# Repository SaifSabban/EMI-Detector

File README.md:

# EMI-Detector
A simple Arduino EMI Detector PCB.
the project mainly following Collin Cunningham's [Video](https://www.youtube.com/watch?v=y1Bke3750WE).

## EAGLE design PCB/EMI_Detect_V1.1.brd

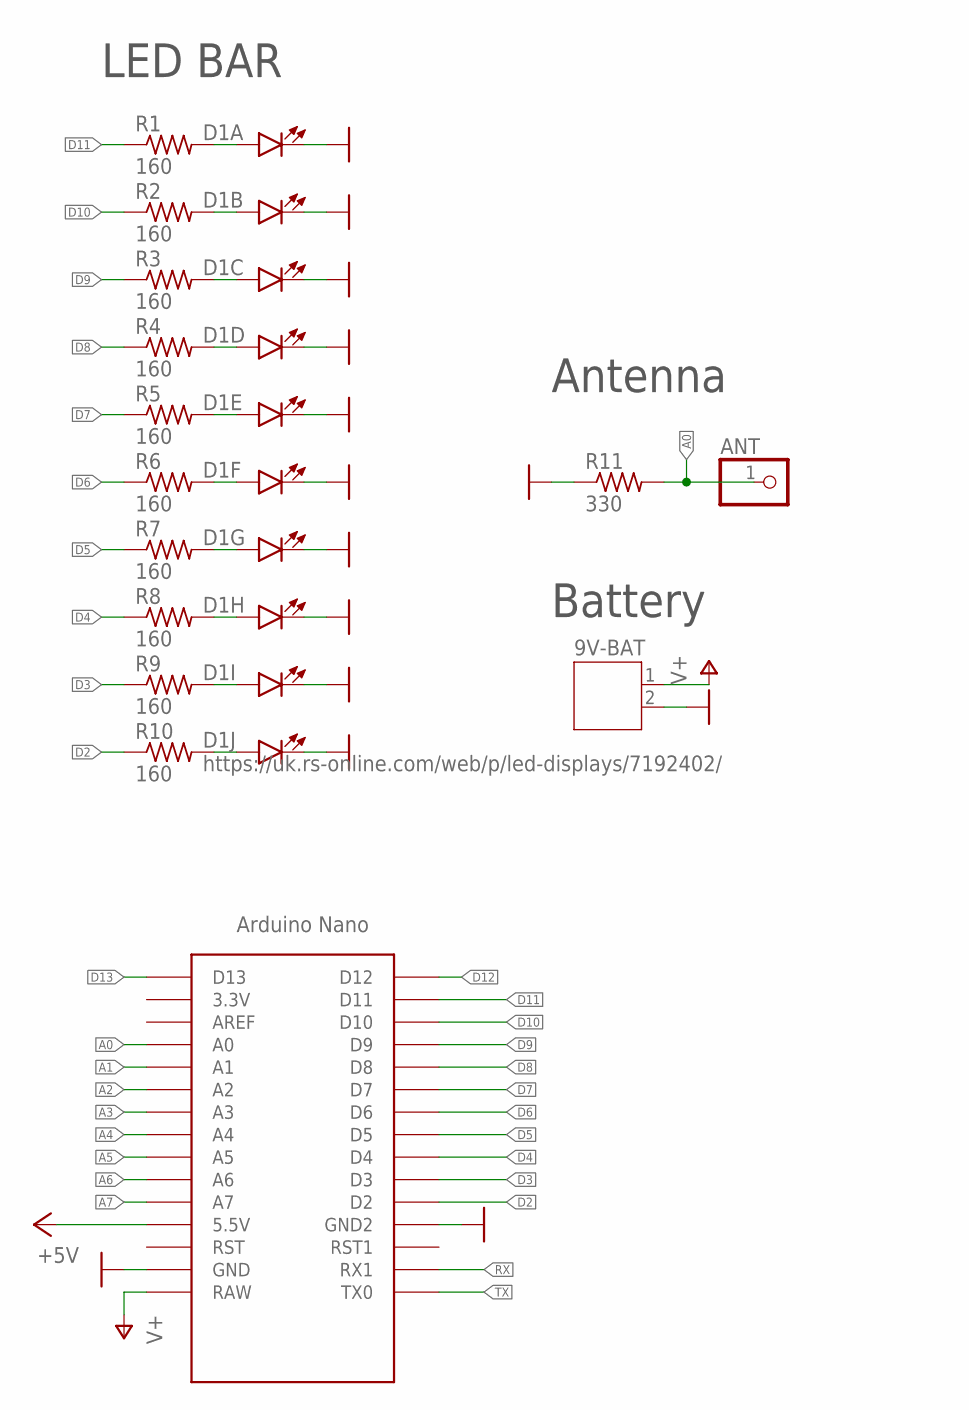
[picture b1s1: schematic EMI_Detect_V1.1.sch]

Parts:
9V-BAT: JST-PH2; JST-PH2-S2B
ANT: PINHD-1X1; 1X01
D1: https://uk.rs-online.com/web/p/led-displays/71924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; LED_BARGAPH_10
R1, R2, R3, R4, R5, R6, R7, R8, R9, R10: 160; R0603
R11: 330; R0603
U1: NANO

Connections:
+5V: U1.5V (5.5V)
A0: ANT.1, R11.2, U1.A0
A1: U1.A1
A2: U1.A2
A3: U1.A3
A4: U1.A4
A5: U1.A5
A6: U1.A6
A7: U1.A7
D2: R10.1, U1.D2
D3: R9.1, U1.D3
D4: R8.1, U1.D4
D5: R7.1, U1.D5
D6: R6.1, U1.D6
D7: R5.1, U1.D7
D8: R4.1, U1.D8
D9: R3.1, U1.D9
D10: R2.1, U1.D10
D11: R1.1, U1.D11
D12: U1.D12
D13: U1.D13
GND: 9V-BAT.2, D1.11 (C), D1.12 (C), D1.13 (C), D1.14 (C), D1.15 (C), D1.16 (C), D1.17 (C), D1.18 (C), D1.19 (C), D1.20 (C), R11.1, U1.GND, U1.GND1 (GND2)
unnamed: D1.1 (A), R1.2
unnamed: D1.2 (A), R2.2
unnamed: D1.3 (A), R3.2
unnamed: D1.4 (A), R4.2
unnamed: D1.5 (A), R5.2
unnamed: D1.6 (A), R6.2
unnamed: D1.7 (A), R7.2
unnamed: D1.8 (A), R8.2
unnamed: D1.9 (A), R9.2
unnamed: D1.10 (A), R10.2
RX: U1.RX1
TX: U1.TX0
V+: 9V-BAT.1, U1.RAW

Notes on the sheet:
LED BAR
Antenna
Battery

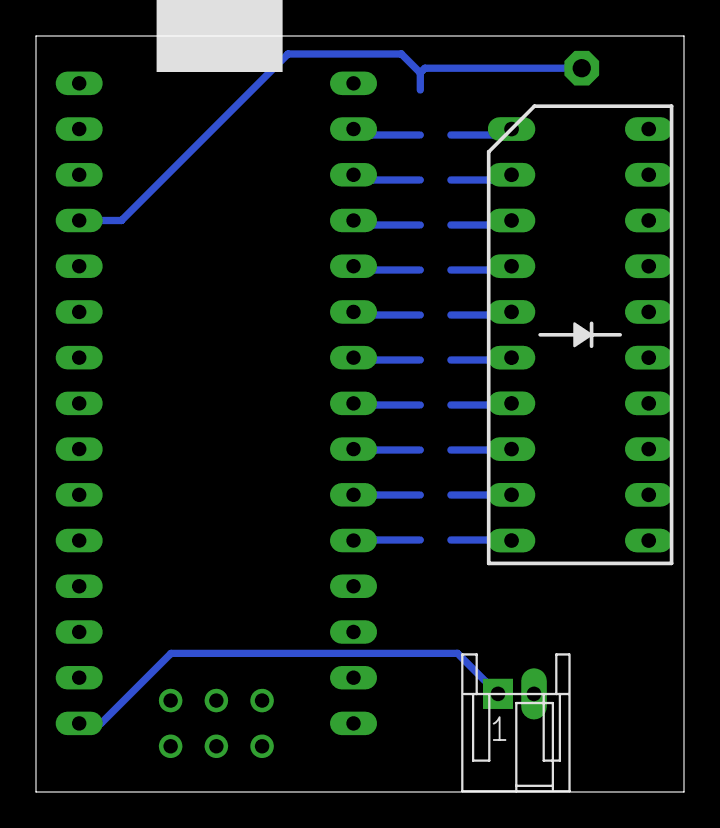
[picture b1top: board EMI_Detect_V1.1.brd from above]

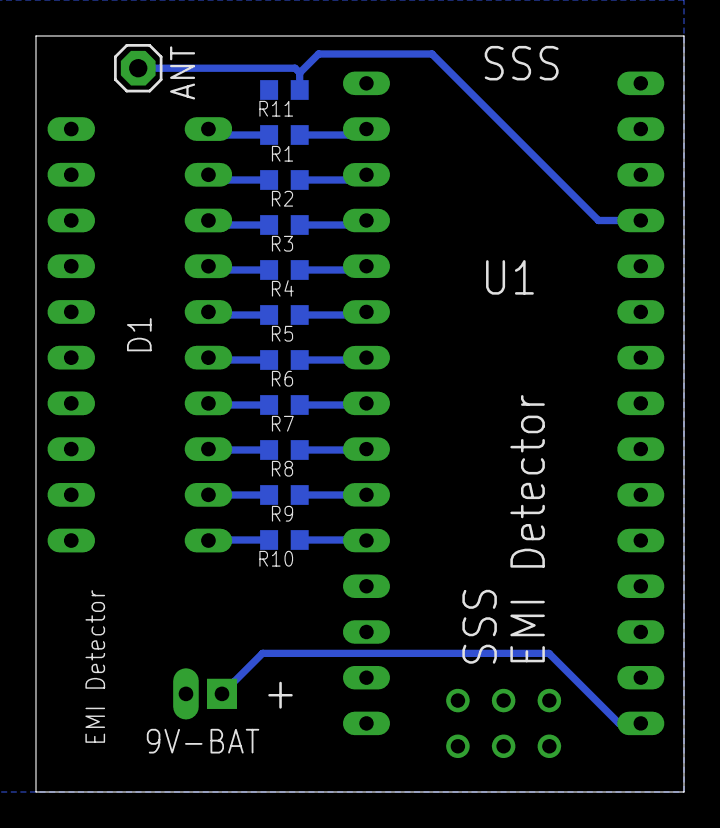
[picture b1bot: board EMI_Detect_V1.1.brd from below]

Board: 2 copper layers, 36.0 x 42.0 mm, 15 parts (12 on the bottom side), 23 nets.

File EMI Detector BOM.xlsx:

Quantity Needed For 1 Machine | Value (For PCB Components) | Device Or Component Name | Package | Description | Where To Buy | Manufacturer | Manufacturers Code | Website Product Code | Cost For Each Component | Minimum Quantity Order | How Many Components Needed For All Machines | How Many Parts To Purchase For All Machines | Costs For Total Parts Needed To Make All Machines | Number of Machines
1 | 10 Bar LED | D1 | Special | Used To indicate how much EMI there is | uk.rs-online.com/web/p/led-displays/7192402/ | Kingbright | DC-10SURKWA | 719-2402 | 0.89 | 2 | 3 | 4 | 3.56 | 3
10 | 160 Ohm | R1, R2, R3, R4, R5, R6, R7, R8, R9, R10 | 0805 | Pull Down Resistor For LEDs | uk.rs-online.com/web/p/surface-mount-fixed-resistors/8280829/ | Panasonic | ERA6AEB161V | 828-0829 | 3.4000000000000002E-2 | 5 | 30 | 30 | 1.02
1 | 2 Pin – PH | 9V-BAT | B2B-PH-K-S | 2 Pin PH Connector | uk.rs-online.com/web/p/pcb-headers/8201422/ | JST (JAPAN SOLDERLESS TERMINALS) | B2B-PH-K-S(LF)(SN) | 820-1422 | 0.38 | 5 | 3 | 5 | 1.9
1 | 330 Ohm | R11 | 0805 | Pull Down Resistor For Antenna | uk.rs-online.com/web/p/surface-mount-fixed-resistors/7217707/ | Panasonic | ERJP06F3300V | 721-7707 | 0.13 | 5 | 3 | 5 | 0.65
1 | 5x DIL, & 2x DIL Connector |  | 5 x DIL | For Possible Expansion | uk.rs-online.com/web/p/pcb-headers/6365230/ | HARWIN | M22-2021846 | 636-5230 | 1.18 | 5 | 3 | 5 | 5.8999999999999995
1 | Arduino Nano Every | EMI Detector | Special | Microcontroller | uk.rs-online.com/web/p/processor-microcontroller-development-kits/1927586/ | Arduino | ABX00028 | 192-7586 | 8.0299999999999994 | 1 | 3 | 3 | 24.089999999999996

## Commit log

2022-05-16 Intial Migration From PC to Github
2022-05-16 Adding Backup Video
2022-05-16 PCB versions

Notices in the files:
parts and their libraries:
SparkFun-LED: Licensing: Creative Commons ShareAlike 4.0 International - https://creativecommons.org/licenses/by-sa/4.0
